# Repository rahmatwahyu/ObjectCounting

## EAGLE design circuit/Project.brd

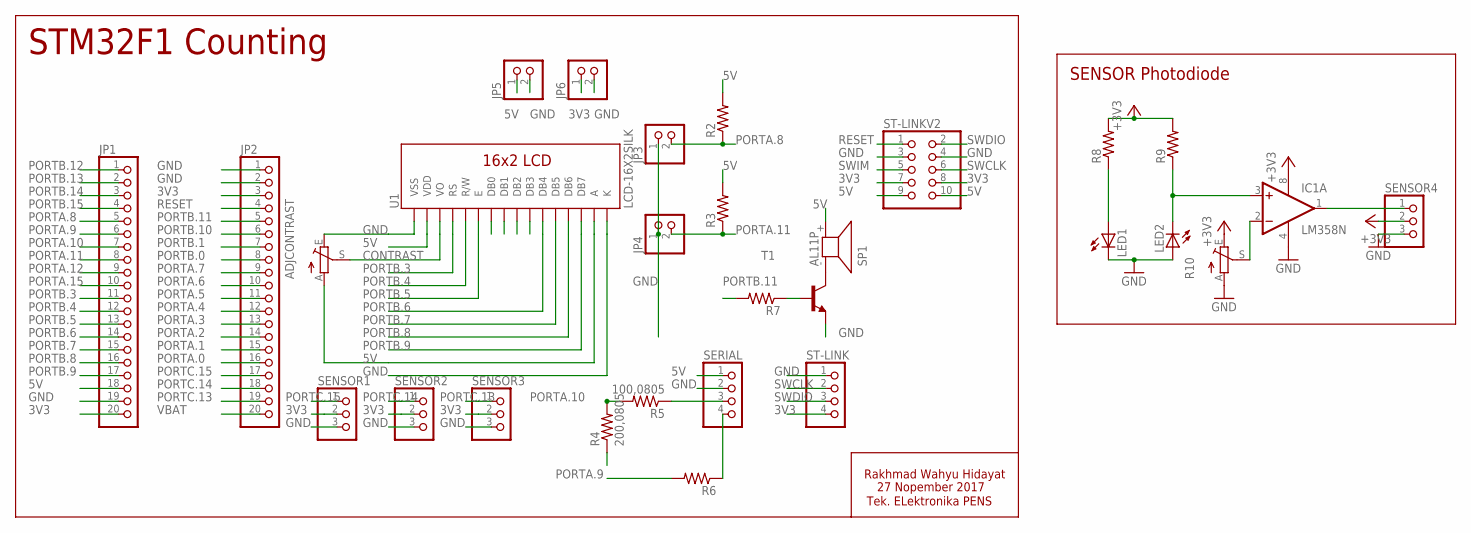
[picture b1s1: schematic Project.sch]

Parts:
ADJCONTRAST: TRIM_EU-CA6V; CA6V
IC1: LM358N; DIL08
JP1, JP2: PINHD-1X20; 1X20
JP3, JP4, JP5, JP6: PINHD-1X2; 1X02
LED1, LED2: LED3MM
R2, R3, R6, R7: R-US_M0805; M0805
R4: 200,0805; M0805
R5: 100,0805; M0805
R8, R9: R-US_0204/7; 0204/7
R10: TRIM_EU-CA6V; CA6V
SENSOR1, SENSOR2, SENSOR3, SENSOR4: PINHD-1X3; 1X03
SERIAL: PINHD-1X4; 1X04
SP1: AL11P
ST-LINK: PINHD-1X4; 1X04
ST-LINKV2: PINHD-2X5; 2X05
T1: -NPN-SOT23-EBC; SOT23-EBC
U1: LCD-16X2SILK; LCD-16X2

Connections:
3V3: JP1.20, JP2.3, JP6.1, SENSOR1.2, SENSOR2.2, SENSOR3.2, ST-LINK.4, ST-LINKV2.7, ST-LINKV2.8
5V: ADJCONTRAST.A, JP1.18, JP5.1, R2.2, R3.2, SERIAL.1, SP1.+ (2), ST-LINKV2.9, ST-LINKV2.10, U1.2 (VDD), U1.15 (A)
+3V3: IC1.8 (V+), R8.2, R9.2, R10.E, SENSOR4.2
CONTRAST: ADJCONTRAST.S, U1.3 (VO)
GND: ADJCONTRAST.E, IC1.4 (V-), JP1.19, JP2.1, JP2.2, JP3.1, JP4.1, JP5.2, JP6.2, LED1.K (C), LED2.A, R4.1, R10.A, SENSOR1.3, SENSOR2.3, SENSOR3.3, SENSOR4.3, SERIAL.2, ST-LINK.1, ST-LINKV2.3, ST-LINKV2.4, T1.E, U1.1 (VSS), U1.16 (K)
unnamed: SP1.- (1), T1.C
unnamed: R7.1, T1.B
unnamed: LED1.A, R8.1
unnamed: IC1.3 (+IN), LED2.K (C), R9.1
unnamed: IC1.2 (-IN), R10.S
unnamed: IC1.1 (OUT), SENSOR4.1
unnamed: R5.1, SERIAL.3
unnamed: R6.1, SERIAL.4
PORTA.0: JP2.16
PORTA.1: JP2.15
PORTA.2: JP2.14
PORTA.3: JP2.13
PORTA.4: JP2.12
PORTA.5: JP2.11
PORTA.6: JP2.10
PORTA.7: JP2.9
PORTA.8: JP1.5, JP3.2, R2.1
PORTA.9: JP1.6, R6.2
PORTA.10: JP1.7, R4.2, R5.2
PORTA.11: JP1.8, JP4.2, R3.1
PORTA.12: JP1.9
PORTA.15: JP1.10
PORTB.0: JP2.8
PORTB.1: JP2.7
PORTB.3: JP1.11, U1.4 (RS)
PORTB.4: JP1.12, U1.5 (R/W)
PORTB.5: JP1.13, U1.6 (E)
PORTB.6: JP1.14, U1.11 (DB4)
PORTB.7: JP1.15, U1.12 (DB5)
PORTB.8: JP1.16, U1.13 (DB6)
PORTB.9: JP1.17, U1.14 (DB7)
PORTB.10: JP2.6
PORTB.11: JP2.5, R7.2
PORTB.12: JP1.1
PORTB.13: JP1.2
PORTB.14: JP1.3
PORTB.15: JP1.4
PORTC.13: JP2.19, SENSOR3.1
PORTC.14: JP2.18, SENSOR2.1
PORTC.15: JP2.17, SENSOR1.1
RESET: JP2.4, ST-LINKV2.1
SWCLK: ST-LINK.2, ST-LINKV2.6
SWDIO: ST-LINK.3, ST-LINKV2.2
SWIM: ST-LINKV2.5
VBAT: JP2.20

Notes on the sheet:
SENSOR Photodiode
STM32F1 Counting
Rakhmad Wahyu Hidayat
27 Nopember 2017
Tek. ELektronika PENS

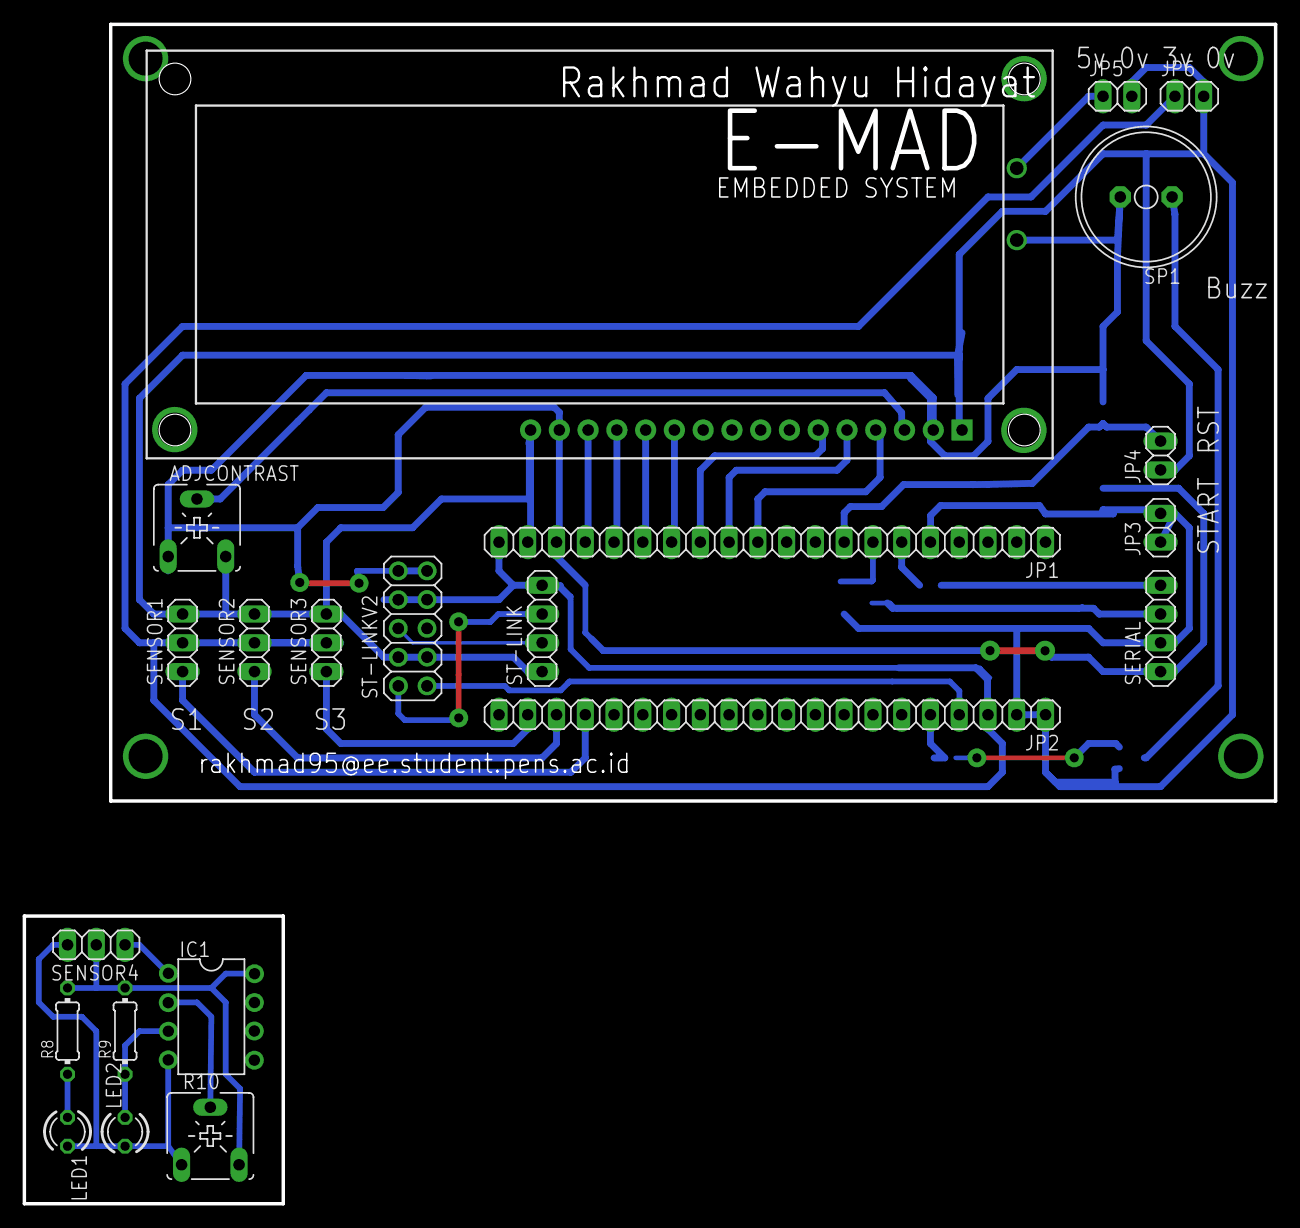
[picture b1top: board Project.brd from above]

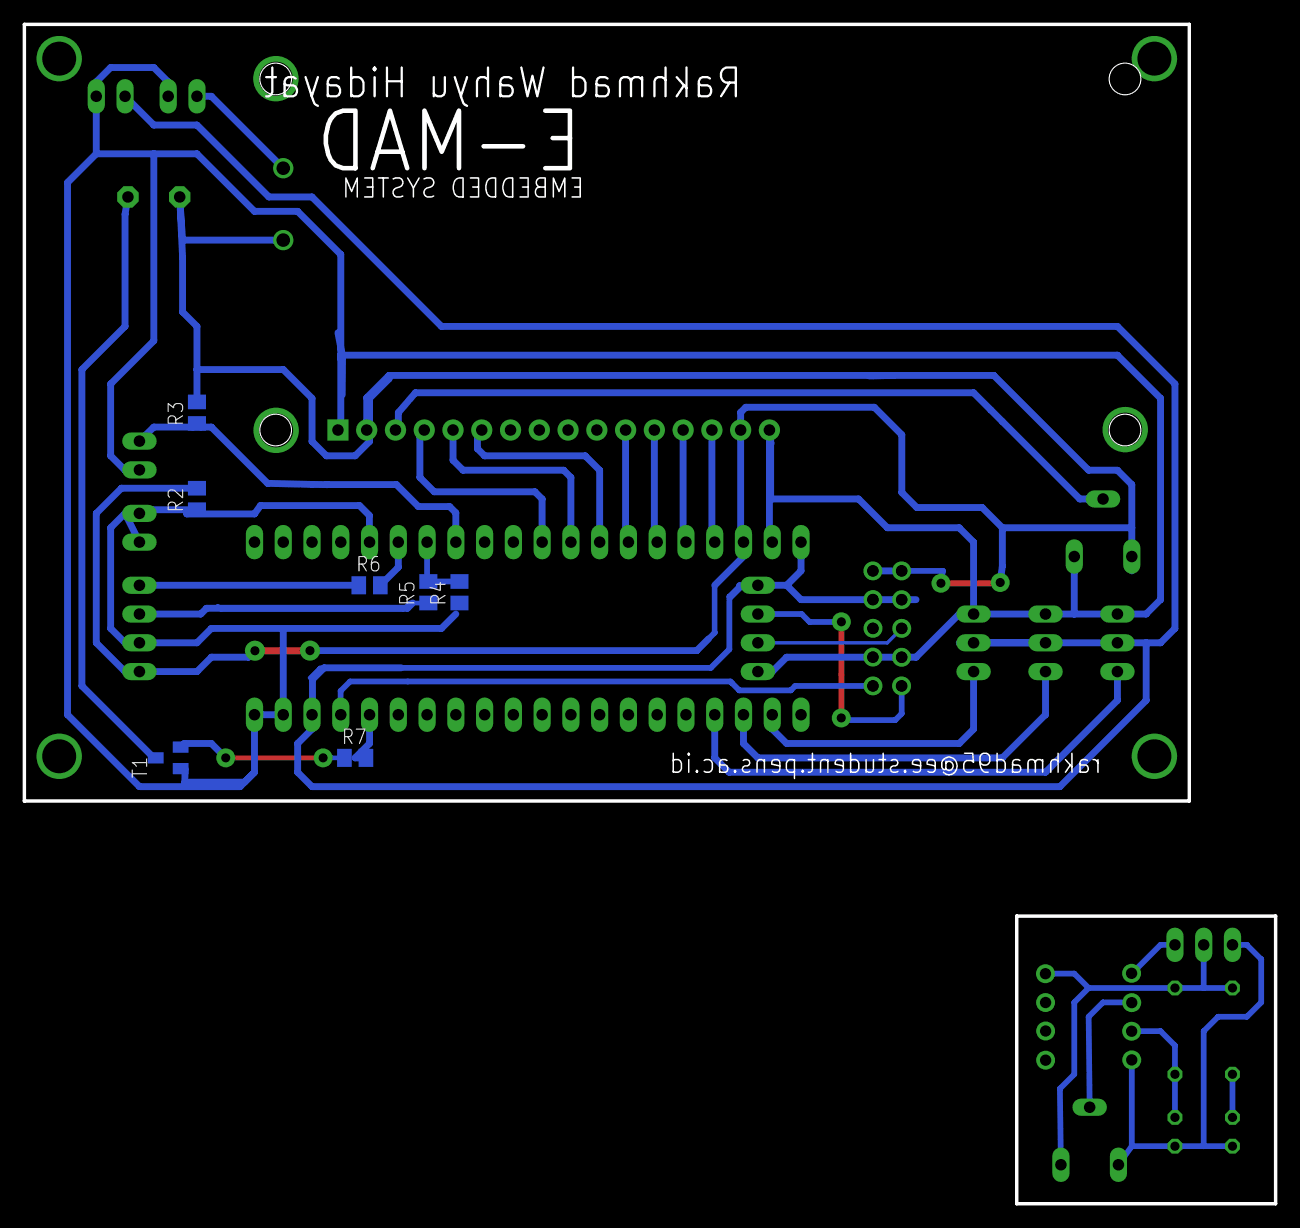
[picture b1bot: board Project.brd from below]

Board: 2 copper layers, 110.5 x 104.1 mm, 29 parts (7 on the bottom side), 31 nets.

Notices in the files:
parts and their libraries:
SparkFun: Licensing: CC v3.0 Share-Alike You are welcome to use this library for commercial purposes.
